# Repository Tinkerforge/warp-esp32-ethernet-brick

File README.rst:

WARP ESP32 Ethernet Brick
=========================

This repository contains the firmware source code and the hardware design
files. The documentation generator configs can be found at
https://github.com/Tinkerforge/generators

.. BEGIN WARP REPOSITORIES (managed block, generated from esp32-firmware/repo_overview.rst - do not edit by hand, run update_repo_overview.py instead)

WARP Repositories
-----------------

This is an overview of all repositories that make up the WARP Charger and
WARP Energy Manager ecosystem.

Please report **any** issue concerning WARP hard- or software in the
`esp32-firmware`_ repository, no matter which repository it originates from.

Software
~~~~~~~~

- `esp32-firmware`_ - Source code of the ESP32 firmware shared between all WARP Chargers and Energy Managers

Libraries used by the firmware:

- `tfjson`_ - SAX style JSON serializer and deserializer
- `tfnetwork`_ - Modbus TCP server and client implementation
- `tfocpp`_ - OCPP 1.6 implementation
- `tftools`_ - Miscellaneous tools and helpers

Remote access:

- `esp32-remote-access`_ - Source code of the my.warp-charger.com remote access server

Documentation, tools and integrations:

- `warp-charger`_ - Source code of (docs.)warp-charger.com and the printed manual, released firmwares, datasheets and documents, as well as some tools and hardware design files
- `api.warp-charger.com`_ - Serves APIs that are used by WARP Chargers to obtain relevant public information like day ahead prices
- `vislog.warp-charger.com`_ - Visualizes WARP Charger logs and EVSE debug protocols
- `dbus-warp-charger`_ - Integrates WARP Chargers into a Victron Energy Venus OS device (e.g. Cerbo GX)

WARP Charger Hardware
~~~~~~~~~~~~~~~~~~~~~~

WARP4 Charger
"""""""""""""

*Current charger generation.*

- `warp-esp32-ethernet-v2-brick`_ - Hardware design files of the WARP ESP32 Ethernet Brick 2.0
- `warp-esp32-ethernet-v2-co-bricklet`_ - Firmware source code of the WARP ESP32 Ethernet 2.0 Co Bricklet (co-processor)
- `evse-v4-bricklet`_ - Hardware design files of the EVSE 4.0 Bricklet (firmware shared with the EVSE 2.0 Bricklet)
- `nfc-bricklet`_ - Firmware source code and hardware design files of the NFC Bricklet

WARP3 Charger
"""""""""""""

- `warp-esp32-ethernet-brick`_ - Hardware design files of the WARP ESP32 Ethernet Brick
- `evse-v3-bricklet`_ - Hardware design files of the EVSE 3.0 Bricklet (firmware shared with the EVSE 2.0 Bricklet)
- `nfc-bricklet`_ - Firmware source code and hardware design files of the NFC Bricklet

WARP2 Charger
"""""""""""""

- `esp32-ethernet-brick`_ - Hardware design files of the ESP32 Ethernet Brick
- `evse-v2-bricklet`_ - Firmware source code and hardware design files of the EVSE 2.0 Bricklet
- `nfc-bricklet`_ - Firmware source code and hardware design files of the NFC Bricklet

WARP1 Charger
"""""""""""""

- `esp32-brick`_ - Hardware design files of the ESP32 Brick
- `evse-bricklet`_ - Firmware source code and hardware design files of the EVSE Bricklet
- `rs485-bricklet`_ - Firmware source code and hardware design files of the RS485 Bricklet

WARP Energy Manager Hardware
~~~~~~~~~~~~~~~~~~~~~~~~~~~~~~

WARP Energy Manager 2.0
"""""""""""""""""""""""

*Current energy manager generation.*

- `esp32-ethernet-brick`_ - Hardware design files of the ESP32 Ethernet Brick
- `warp-energy-manager-v2-bricklet`_ - Firmware source code and hardware design files of the WARP Energy Manager 2.0 Bricklet
- `warp-front-panel-bricklet`_ - Firmware source code and hardware design files of the WARP Front Panel Bricklet

WARP Energy Manager 1.0
"""""""""""""""""""""""

- `esp32-ethernet-brick`_ - Hardware design files of the ESP32 Ethernet Brick
- `warp-energy-manager-bricklet`_ - Firmware source code and hardware design files of the WARP Energy Manager Bricklet

Forked/patched projects
~~~~~~~~~~~~~~~~~~~~~~~~~

- `arduino-esp32`_
- `esp32-arduino-libs`_
- `WireGuard-ESP32-Arduino`_

.. Link targets: One definition per repository, keep in sync with the lists above.

.. _esp32-firmware: https://github.com/Tinkerforge/esp32-firmware
.. _tfjson: https://github.com/Tinkerforge/tfjson
.. _tfnetwork: https://github.com/Tinkerforge/tfnetwork
.. _tfocpp: https://github.com/Tinkerforge/tfocpp
.. _tftools: https://github.com/Tinkerforge/tftools
.. _esp32-remote-access: https://github.com/Tinkerforge/esp32-remote-access
.. _warp-charger: https://github.com/Tinkerforge/warp-charger
.. _api.warp-charger.com: https://github.com/Tinkerforge/api.warp-charger.com
.. _vislog.warp-charger.com: https://github.com/Tinkerforge/vislog.warp-charger.com
.. _dbus-warp-charger: https://github.com/Tinkerforge/dbus-warp-charger
.. _warp-esp32-ethernet-v2-brick: https://github.com/Tinkerforge/warp-esp32-ethernet-v2-brick
.. _warp-esp32-ethernet-v2-co-bricklet: https://github.com/Tinkerforge/warp-esp32-ethernet-v2-co-bricklet
.. _evse-v4-bricklet: https://github.com/Tinkerforge/evse-v4-bricklet
.. _nfc-bricklet: https://github.com/Tinkerforge/nfc-bricklet
.. _warp-esp32-ethernet-brick: https://github.com/Tinkerforge/warp-esp32-ethernet-brick
.. _evse-v3-bricklet: https://github.com/Tinkerforge/evse-v3-bricklet
.. _esp32-ethernet-brick: https://github.com/Tinkerforge/esp32-ethernet-brick
.. _evse-v2-bricklet: https://github.com/Tinkerforge/evse-v2-bricklet
.. _esp32-brick: https://github.com/Tinkerforge/esp32-brick
.. _evse-bricklet: https://github.com/Tinkerforge/evse-bricklet
.. _rs485-bricklet: https://github.com/Tinkerforge/rs485-bricklet
.. _warp-energy-manager-v2-bricklet: https://github.com/Tinkerforge/warp-energy-manager-v2-bricklet
.. _warp-front-panel-bricklet: https://github.com/Tinkerforge/warp-front-panel-bricklet
.. _warp-energy-manager-bricklet: https://github.com/Tinkerforge/warp-energy-manager-bricklet
.. _arduino-esp32: https://github.com/Tinkerforge/arduino-esp32
.. _esp32-arduino-libs: https://github.com/Tinkerforge/esp32-arduino-libs
.. _WireGuard-ESP32-Arduino: https://github.com/Tinkerforge/WireGuard-ESP32-Arduino

.. END WARP REPOSITORIES

Repository Content
------------------

hardware/:
 * Contains KiCad project files and additionally schematics as PDF

datasheets/:
 * Contains datasheets for sensors and complex ICs that are used

Hardware
--------

The hardware is designed with the open source EDA Suite KiCad
(http://www.kicad.org). Before you are able to open the files,
you have to install the Tinkerforge kicad-libraries
(https://github.com/Tinkerforge/kicad-libraries). You can either clone
them directly in hardware/ or clone them in a separate folder and
symlink them into hardware/
(ln -s kicad_path/kicad-libraries project_path/hardware). After that you
can open the .pro file in hardware/ with KiCad and from there view and
modify the schematics and the PCB layout.

Software
--------

The software for all Bricks based on the ESP32 can be found at:
https://github.com/Tinkerforge/esp32-firmware/tree/master/software

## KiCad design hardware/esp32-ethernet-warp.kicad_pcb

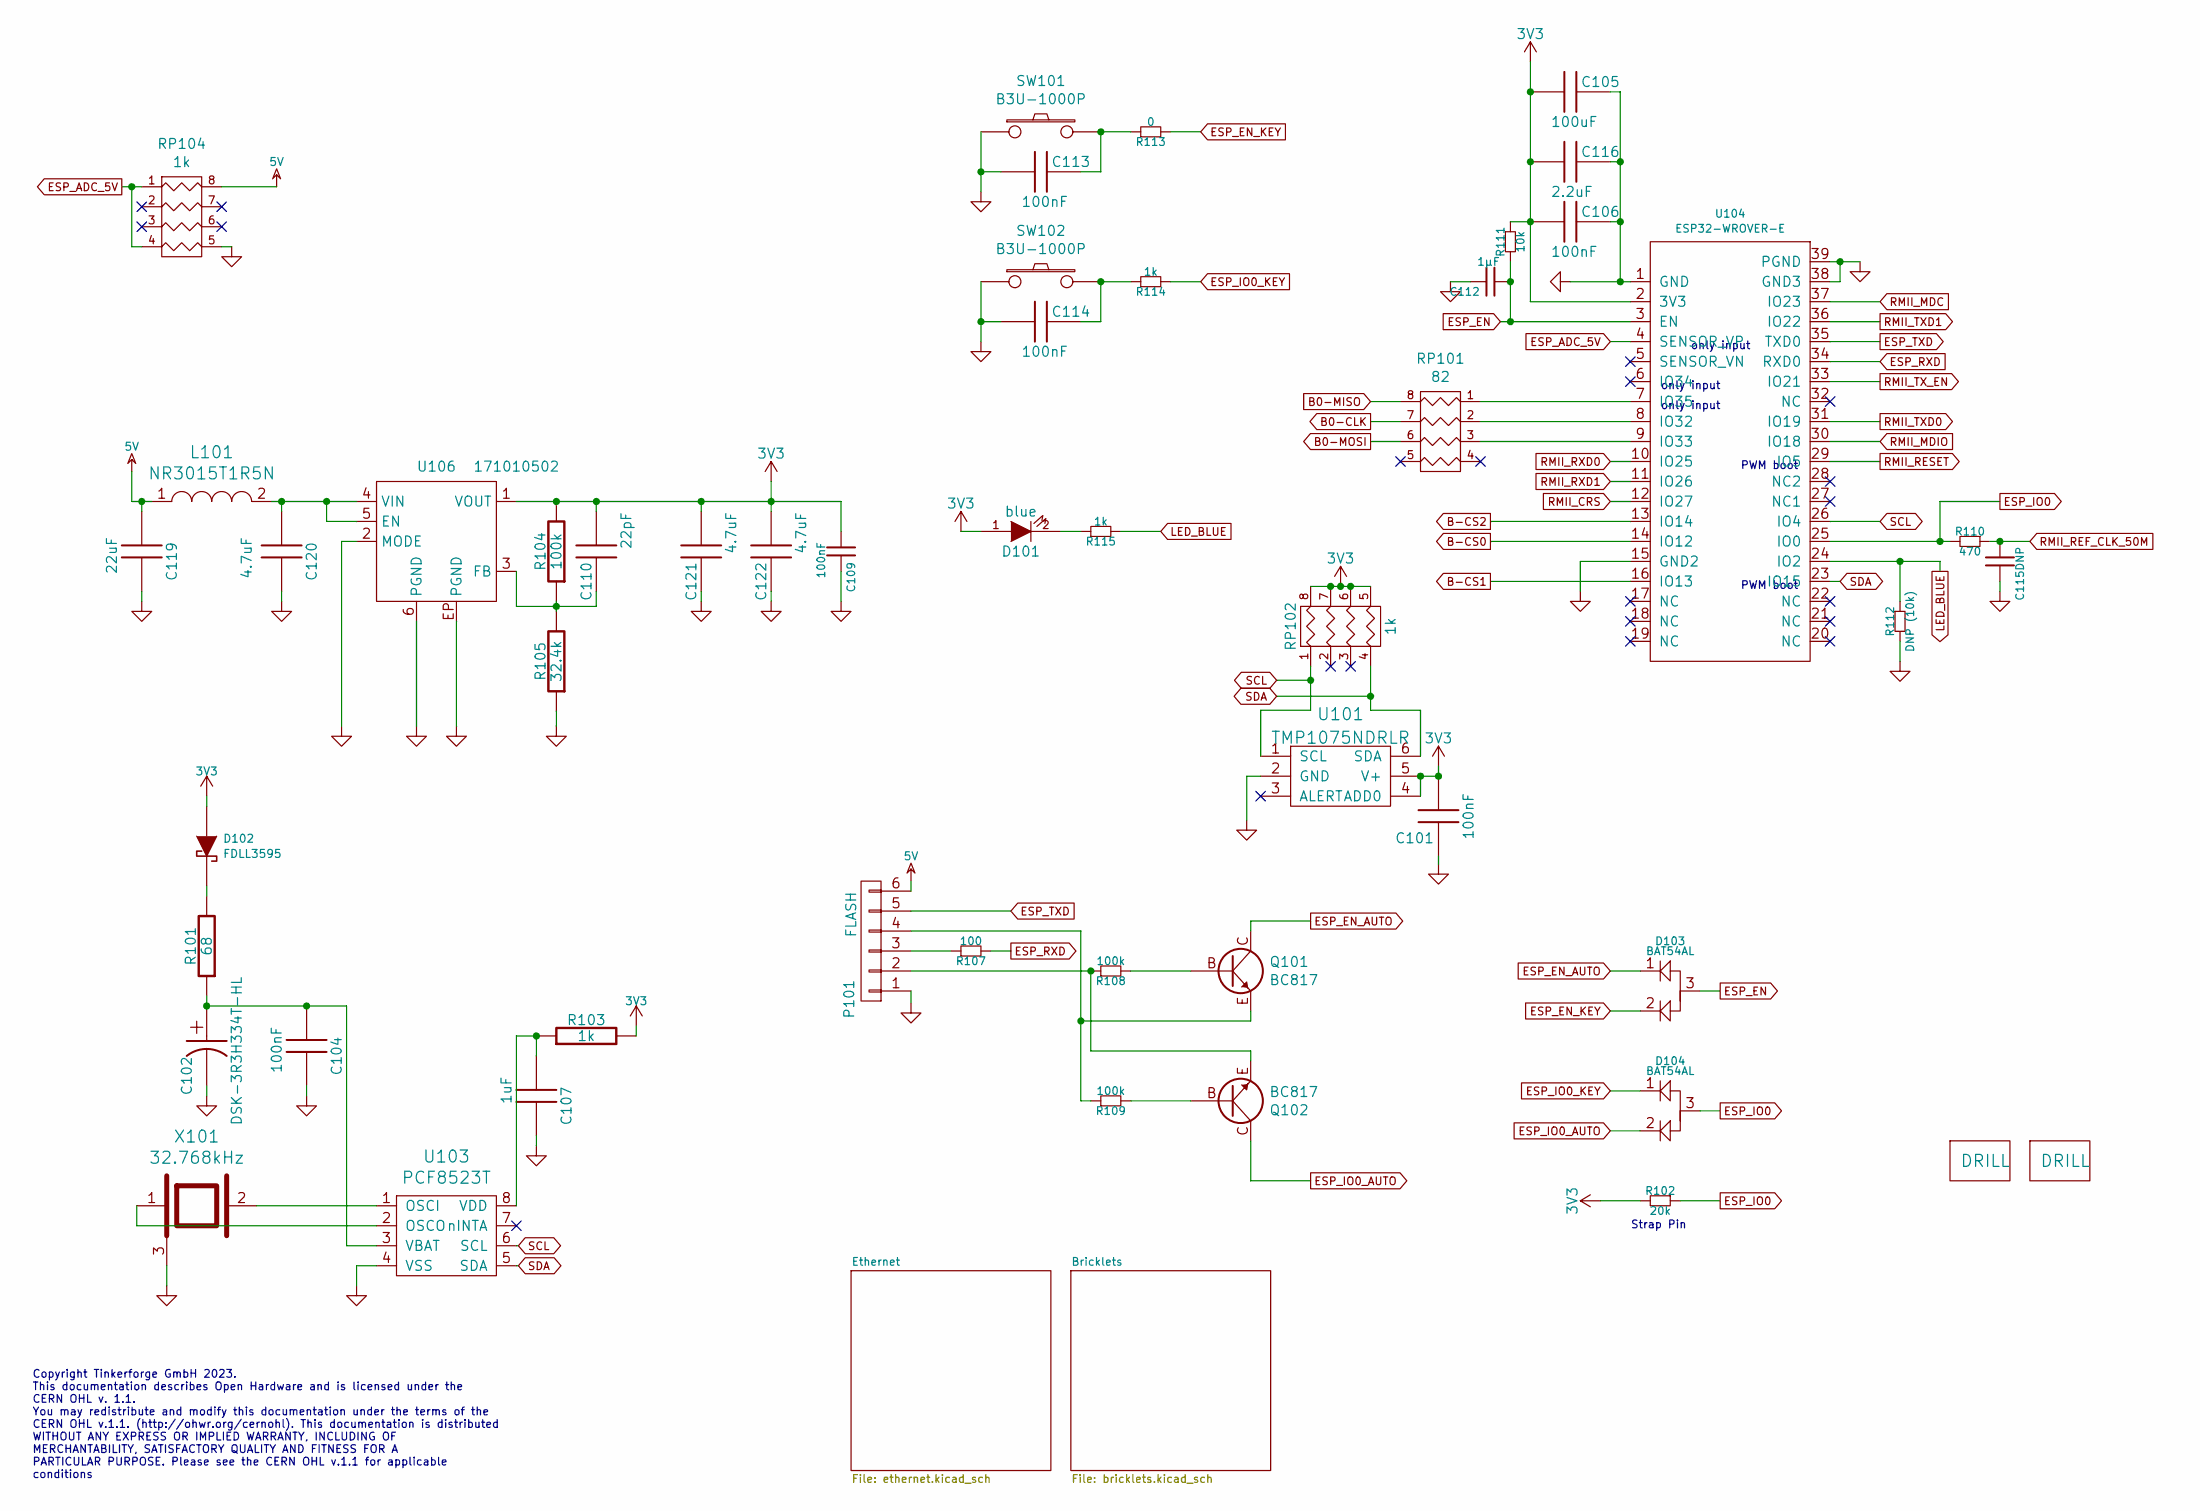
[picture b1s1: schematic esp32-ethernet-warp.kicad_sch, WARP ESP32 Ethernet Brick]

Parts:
C101, C104, C106, C109, C113, C114: 100nF; C0402F
C102: DSK-3R3H334T-HL; DSK
C105: 100uF; C1210
C107: 1uF; C0603F
C110: 22pF; C0402F
C112: 1µF; C0603F
C115: DNP; C0402F
C116: 2.2uF; C0603F
C119: 22uF; C1206
C120, C121, C122: 4.7uF; C0805E
D101: blue; D0603F
D102: FDLL3595; MiniMelf
D103, D104: BAT54AL; SOT23-3
F102, F103: DRILL; LSMTSO-M3
L101: NR3015T1R5N; NR3030
P101: FLASH; pin_array_1x6-P2mm_D1mm
Q101, Q102: BC817; SOT23EBC
R101: 68; R0402F
R102: 20k; R0402F
R103, R114, R115: 1k; R0402F
R104, R108, R109: 100k; R0402F
R105: 32.4k; R0402F
R107: 100; R0402F
R110: 470; R0402F
R111: 10k; R0402F
R112: DNP (10k); R0402F
R113: 0; R0402F
RP101: 82; 4X0402
RP102, RP104: 1k; 4X0402
SW101, SW102: B3U-1000P
U101: TMP1075NDRLR; SOT563
U103: PCF8523T; SO-8
U104: ESP32-WROVER-E
U106: 171010502
X101: 32.768kHz; AB26TRQ

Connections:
3V3: C101.1, C105.2, C106.2, C109.2, C110.2, C116.2, C121.2, C122.2, D101.1 (A), D102.1 (A), R102.2, R103.2, R104.2, R111.1, RP102.5 (R4), RP102.6 (R3), RP102.7 (R2), RP102.8 (R1), U101.4 (ADD0), U101.5 (V+), U104.2 (3V3), U106.1 (VOUT); also elsewhere on the board
5V: C119.2, L101.1, P101.6, RP104.8 (R1); also elsewhere on the board
B0-CLK: RP101.7 (R2); also elsewhere on the board
B0-MISO: RP101.8 (R1); also elsewhere on the board
B0-MOSI: RP101.6 (R3); also elsewhere on the board
B-CS0: U104.14 (IO12); also elsewhere on the board
B-CS1: U104.16 (IO13); also elsewhere on the board
B-CS2: U104.13 (IO14); also elsewhere on the board
ESP_ADC_5V: RP104.1, RP104.4, U104.4 (SENSOR_VP)
ESP_EN: C112.2, D103.3, R111.2, U104.3 (EN)
ESP_EN_AUTO: D103.1, Q101.C
ESP_EN_KEY: D103.2, R113.2
ESP_IO0: D104.3, R102.1, R110.2, U104.25 (IO0)
ESP_IO0_AUTO: D104.2, Q102.C
ESP_IO0_KEY: D104.1, R114.2
ESP_RXD: R107.2, U104.34 (RXD0)
ESP_TXD: P101.5, U104.35 (TXD0)
GND: C101.2, C102.2, C104.1, C105.1, C106.1, C107.1, C109.1, C112.1, C113.2, C114.2, C115.2, C116.1, C119.1, C120.1, C121.1, C122.1, P101.1, R105.1, R112.2, RP104.5 (R4), SW101.1, SW102.1, U101.2 (GND), U103.4 (VSS), U104.1 (GND), U104.15 (GND2), U104.38 (GND3), U104.39 (PGND), U106.2 (MODE), U106.6 (PGND), U106.EP (PGND), X101.3; also elsewhere on the board
LED_BLUE: R112.1, R115.2, U104.24 (IO2)
unnamed: C113.1, R113.1, SW101.2
unnamed: C114.1, R114.1, SW102.2
unnamed: D101.2 (K), R115.1
unnamed: D102.2 (K), R101.2
unnamed: P101.2, Q102.E, R108.1
unnamed: P101.3, R107.1
unnamed: P101.4, Q101.E, R109.1
unnamed: Q101.B, R108.2
unnamed: Q102.B, R109.2
unnamed: RP101.1, U104.7 (IO35)
unnamed: RP101.2, U104.8 (IO32)
unnamed: RP101.3, U104.9 (IO33)
unnamed: U103.1 (OSCI), X101.2
unnamed: U103.2 (OSCO), X101.1
unnamed: C102.1, C104.2, R101.1, U103.3 (VBAT)
unnamed: C107.2, R103.1, U103.8 (VDD)
unnamed: C120.2, L101.2, U106.4 (VIN), U106.5 (EN)
unnamed: C110.1, R104.1, R105.2, U106.3 (FB)
RMII_CRS: U104.12 (IO27); also elsewhere on the board
RMII_MDC: U104.37 (IO23); also elsewhere on the board
RMII_MDIO: U104.30 (IO18); also elsewhere on the board
RMII_REF_CLK_50M: C115.1, R110.1; also elsewhere on the board
RMII_RESET: U104.29 (IO5); also elsewhere on the board
RMII_RXD0: U104.10 (IO25); also elsewhere on the board
RMII_RXD1: U104.11 (IO26); also elsewhere on the board
RMII_TXD0: U104.31 (IO19); also elsewhere on the board
RMII_TXD1: U104.36 (IO22); also elsewhere on the board
RMII_TX_EN: U104.33 (IO21); also elsewhere on the board
SCL: RP102.1, U101.1 (SCL), U103.6 (SCL), U104.26 (IO4)
SDA: RP102.4, U101.6 (SDA), U103.5 (SDA), U104.23 (IO15)

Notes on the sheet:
Strap Pin
only input
Copyright Tinkerforge GmbH 2023. This documentation describes Open Hardware and is licensed under the CERN OHL v. 1.1. You may redistribute and modify this documentation under the terms of the CERN OHL v.1.1. (http://ohwr.org/cernohl). This documentation is distributed WITHOUT ANY EXPRESS OR IMPLIE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
PWM boot

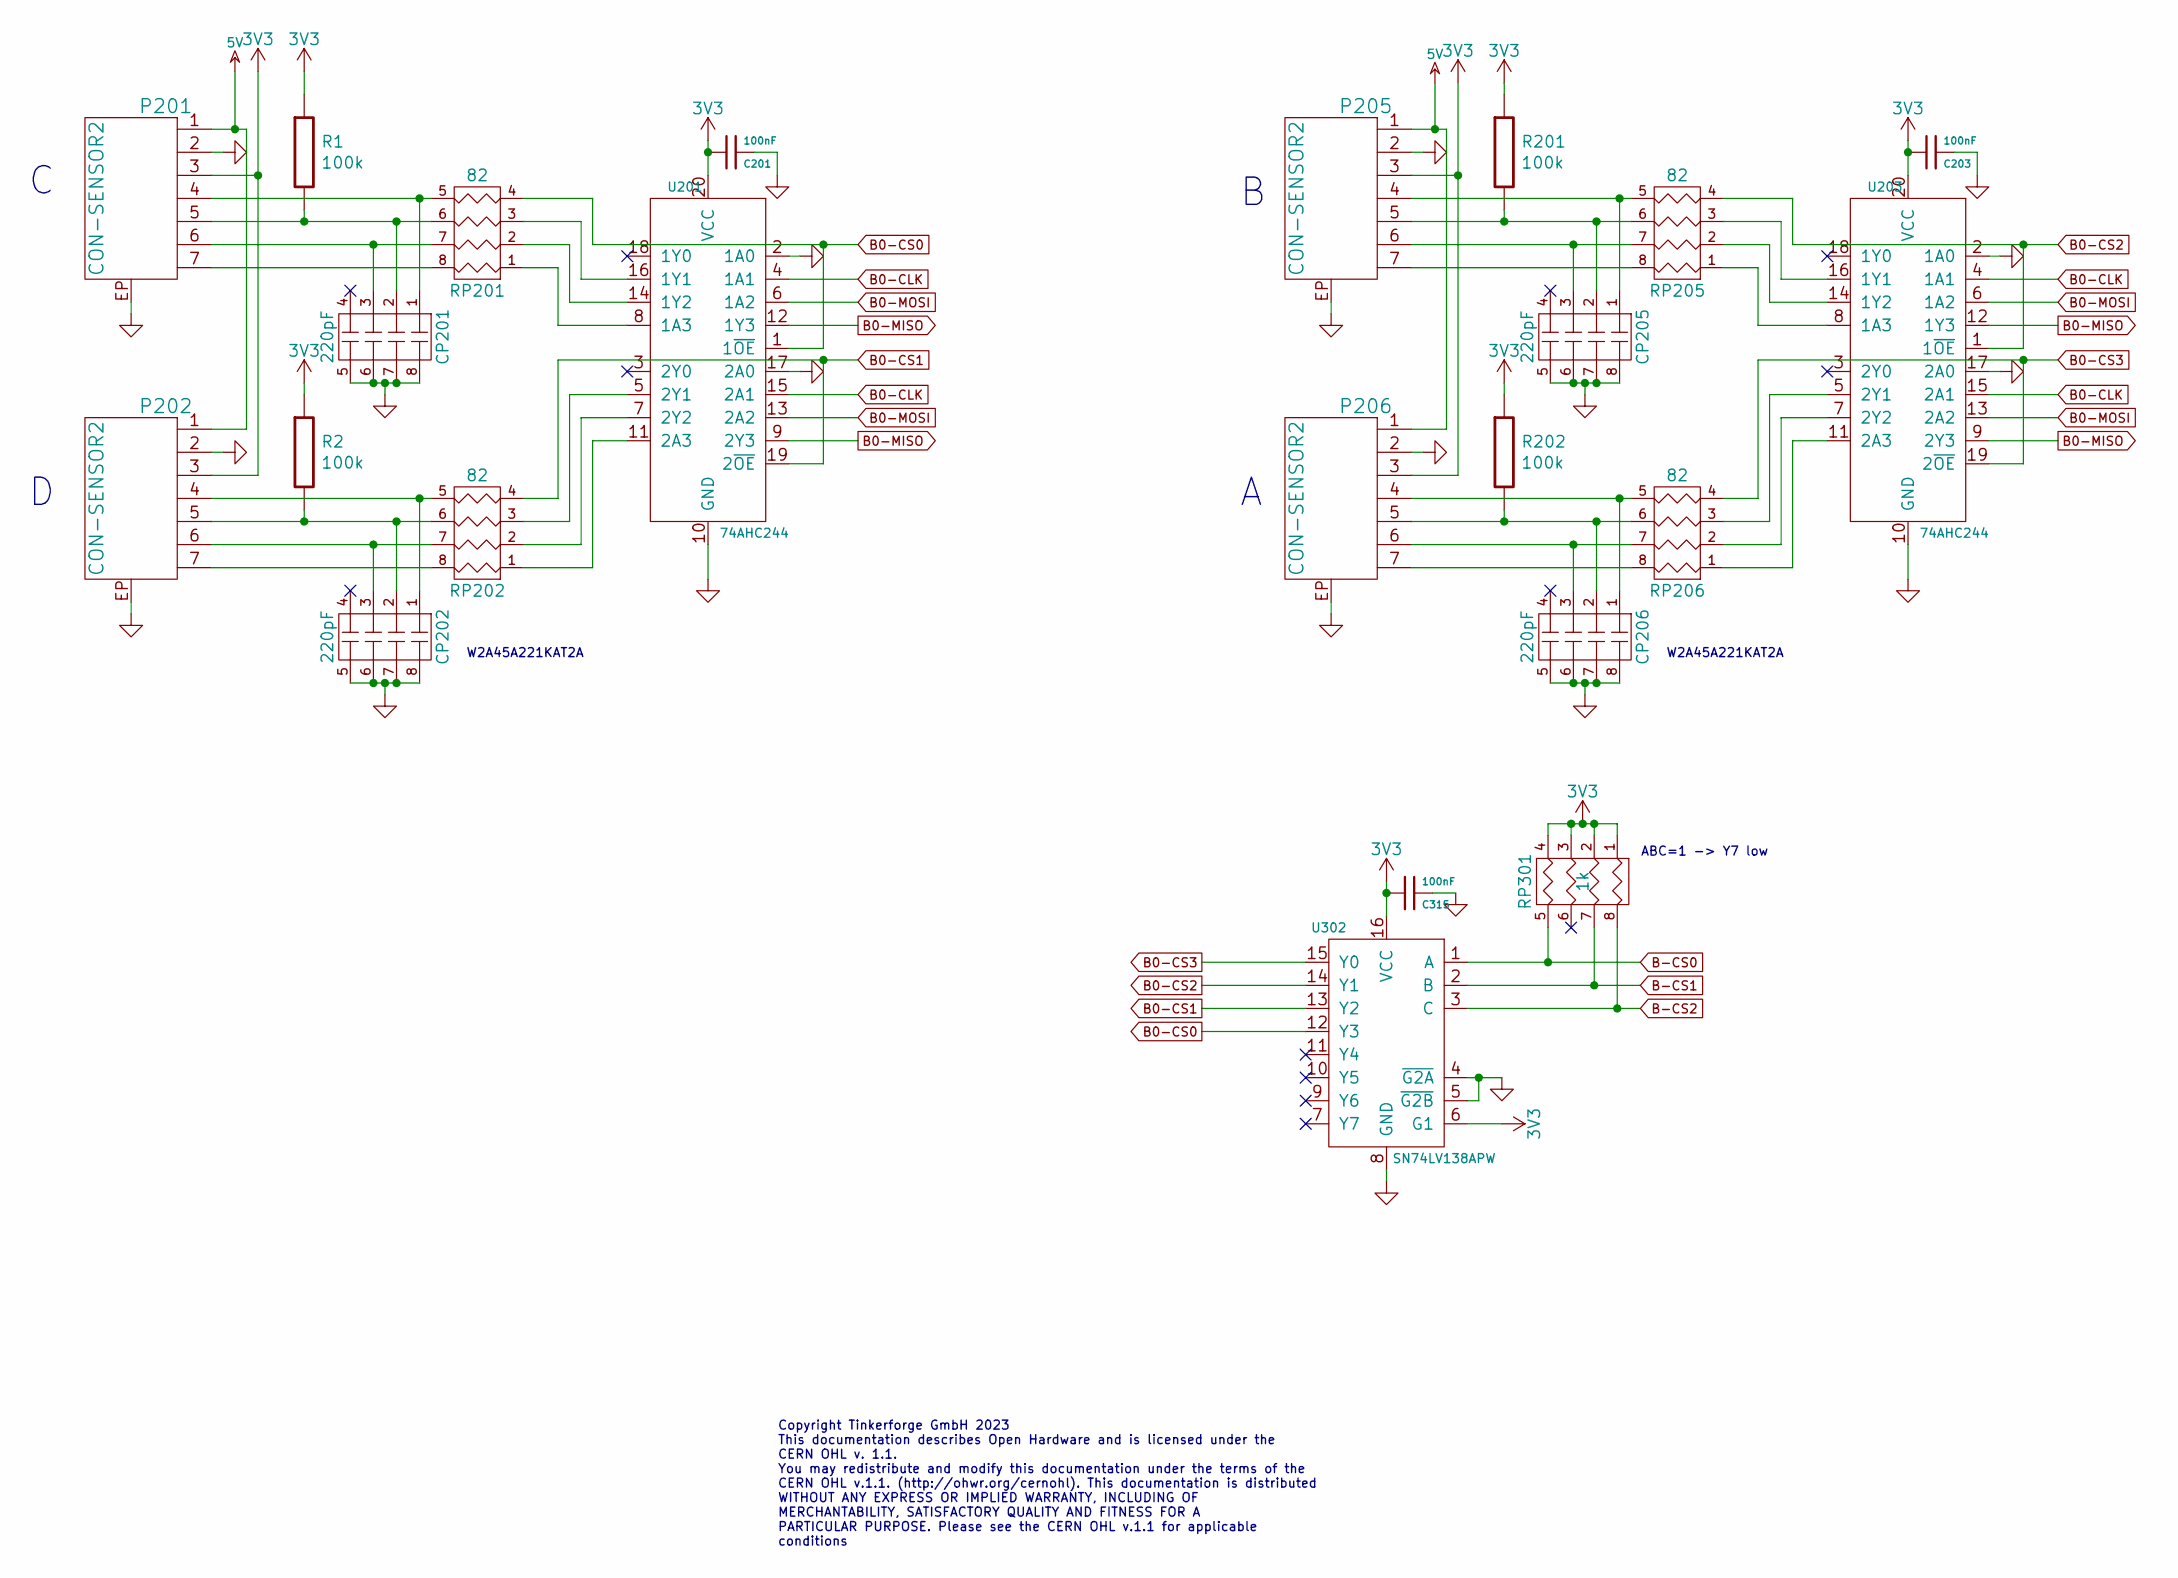
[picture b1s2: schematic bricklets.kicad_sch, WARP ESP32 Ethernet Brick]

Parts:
C201, C203, C315: 100nF; C0402F
CP201, CP202, CP205, CP206: 220pF; 4X0402
P201, P202, P205, P206: CON-SENSOR2
R1, R2, R201, R202: 100k; R0402F
RP201, RP202, RP205, RP206: 82; 4X0402
RP301: 1k; 4X0402
U201, U203: 74AHC244; TSSOP20
U302: SN74LV138APW; TSSOP16

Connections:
3V3: C201.2, C203.2, C315.2, P201.3, P202.3, P205.3, P206.3, R1.1, R2.1, R201.1, R202.1, RP301.1, RP301.2, RP301.3, RP301.4, U201.20 (VCC), U203.20 (VCC), U302.6 (G1), U302.16 (VCC); also elsewhere on the board
5V: P201.1, P202.1, P205.1, P206.1; also elsewhere on the board
B0-CLK: U201.4 (1A1), U201.15 (2A1), U203.4 (1A1), U203.15 (2A1); also elsewhere on the board
B0-CS0: RP201.4, U201.1 (1~OE), U302.12 (Y3)
B0-CS1: RP202.4, U201.19 (2~OE), U302.13 (Y2)
B0-CS2: RP205.4, U203.1 (1~OE), U302.14 (Y1)
B0-CS3: RP206.4, U203.19 (2~OE), U302.15 (Y0)
B0-MISO: U201.9 (2Y3), U201.12 (1Y3), U203.9 (2Y3), U203.12 (1Y3); also elsewhere on the board
B0-MOSI: U201.6 (1A2), U201.13 (2A2), U203.6 (1A2), U203.13 (2A2); also elsewhere on the board
B-CS0: RP301.5 (R4), U302.1 (A); also elsewhere on the board
B-CS1: RP301.7 (R2), U302.2 (B); also elsewhere on the board
B-CS2: RP301.8 (R1), U302.3 (C); also elsewhere on the board
GND: C201.1, C203.1, C315.1, CP201.5 (R4), CP201.6 (R3), CP201.7 (R2), CP201.8 (R1), CP202.5 (R4), CP202.6 (R3), CP202.7 (R2), CP202.8 (R1), CP205.5 (R4), CP205.6 (R3), CP205.7 (R2), CP205.8 (R1), CP206.5 (R4), CP206.6 (R3), CP206.7 (R2), CP206.8 (R1), P201.2, P201.EP, P202.2, P202.EP, P205.2, P205.EP, P206.2, P206.EP, U201.2 (1A0), U201.10 (GND), U201.17 (2A0), U203.2 (1A0), U203.10 (GND), U203.17 (2A0), U302.4 (~G2A), U302.5 (~G2B), U302.8 (GND); also elsewhere on the board
unnamed: CP201.1, P201.4, RP201.5 (R4)
unnamed: CP201.2, P201.5, R1.2, RP201.6 (R3)
unnamed: CP201.3, P201.6, RP201.7 (R2)
unnamed: CP202.1, P202.4, RP202.5 (R4)
unnamed: CP202.2, P202.5, R2.2, RP202.6 (R3)
unnamed: CP202.3, P202.6, RP202.7 (R2)
unnamed: CP205.1, P205.4, RP205.5 (R4)
unnamed: CP205.2, P205.5, R201.2, RP205.6 (R3)
unnamed: CP205.3, P205.6, RP205.7 (R2)
unnamed: CP206.1, P206.4, RP206.5 (R4)
unnamed: CP206.2, P206.5, R202.2, RP206.6 (R3)
unnamed: CP206.3, P206.6, RP206.7 (R2)
unnamed: RP201.1, U201.8 (1A3)
unnamed: RP201.2, U201.14 (1Y2)
unnamed: RP201.3, U201.16 (1Y1)
unnamed: P201.7, RP201.8 (R1)
unnamed: RP202.1, U201.11 (2A3)
unnamed: RP202.2, U201.7 (2Y2)
unnamed: RP202.3, U201.5 (2Y1)
unnamed: P202.7, RP202.8 (R1)
unnamed: RP205.1, U203.8 (1A3)
unnamed: RP205.2, U203.14 (1Y2)
unnamed: RP205.3, U203.16 (1Y1)
unnamed: P205.7, RP205.8 (R1)
unnamed: RP206.1, U203.11 (2A3)
unnamed: RP206.2, U203.7 (2Y2)
unnamed: RP206.3, U203.5 (2Y1)
unnamed: P206.7, RP206.8 (R1)

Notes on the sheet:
Copyright Tinkerforge GmbH 2023 This documentation describes Open Hardware and is licensed under the CERN OHL v. 1.1. You may redistribute and modify this documentation under the terms of the CERN OHL v.1.1. (http://ohwr.org/cernohl). This documentation is distributed WITHOUT ANY EXPRESS OR IMPLIED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
W2A45A221KAT2A
ABC=1 -> Y7 low

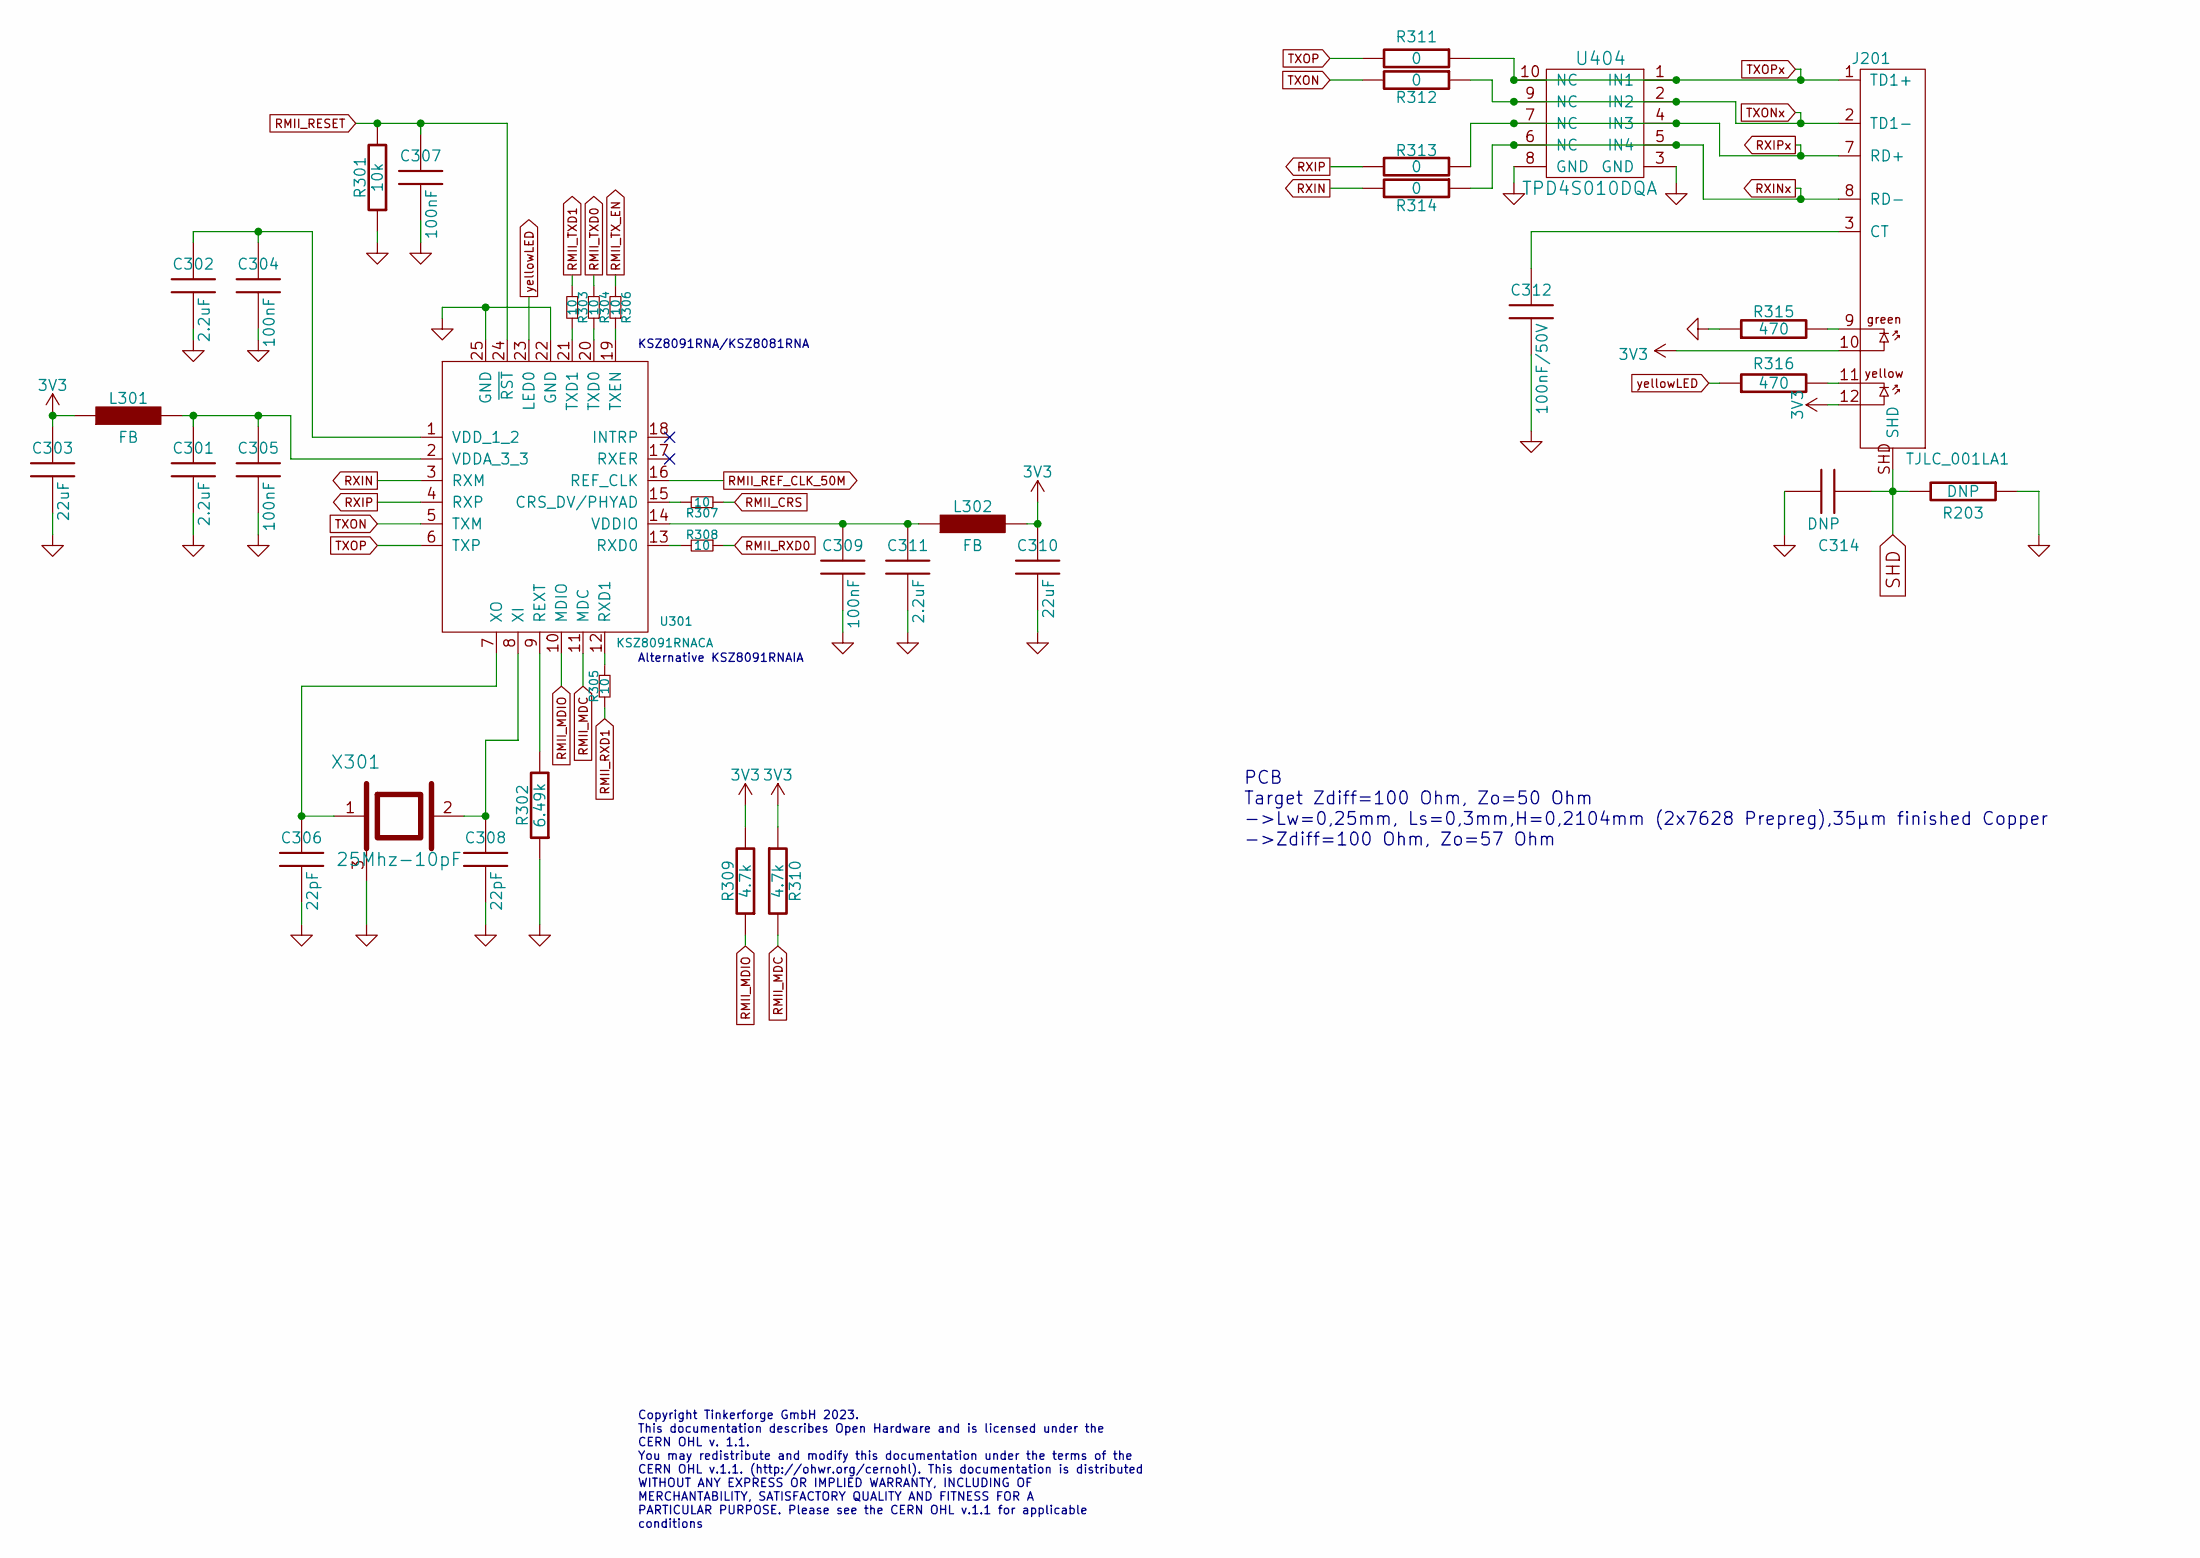
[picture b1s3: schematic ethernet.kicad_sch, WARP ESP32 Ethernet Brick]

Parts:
C301, C302, C311: 2.2uF; C0603F
C303, C310: 22uF; C1206
C304, C305, C307, C309: 100nF; C0402F
C306, C308: 22pF; C0402F
C312: 100nF/50V; C0402F
C314: DNP; C1206
J201: TJLC_001LA1; TJLC-001LA1
L301, L302: FB; R0603F
R203: DNP; 1812
R301: 10k; R0402F
R302: 6.49k; R0402F
R303, R304, R305, R306, R307, R308: 10; R0402F
R309, R310: 4.7k; R0402F
R311, R312, R313, R314: 0; R0402F
R315, R316: 470; R0402F
U301: KSZ8091RNACA; QFN-24-4x4-EP
U404: TPD4S010DQA
X301: 25Mhz-10pF; CRYSTAL_3225

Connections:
3V3: C303.2, C310.2, J201.10, J201.12, L301.1, L302.2, R309.2, R310.1; also elsewhere on the board
GND: C301.1, C302.1, C303.1, C304.1, C305.1, C306.1, C307.1, C308.1, C309.1, C310.1, C311.1, C312.1, C314.2, R203.1, R301.1, R302.1, R315.1, U301.22 (GND), U301.25 (GND), X301.3; also elsewhere on the board
unnamed: C312.2, J201.3 (CT)
unnamed: J201.9, R315.2
unnamed: J201.11, R316.2
unnamed: R307.1, U301.15 (CRS_DV/PHYAD)
unnamed: R302.2, U301.9 (REXT)
unnamed: R308.2, U301.13 (RXD0)
unnamed: R305.1, U301.12 (RXD1)
unnamed: R304.1, U301.20 (TXD0)
unnamed: R303.1, U301.21 (TXD1)
unnamed: R306.1, U301.19 (TXEN)
unnamed: C301.2, C305.2, L301.2, U301.2 (VDDA_3_3)
unnamed: C309.2, C311.2, L302.1, U301.14 (VDDIO)
unnamed: C302.2, C304.2, U301.1 (VDD_1_2)
unnamed: C308.2, U301.8 (XI), X301.2
unnamed: C306.2, U301.7 (XO), X301.1
RMII_CRS: R307.2; also elsewhere on the board
RMII_MDC: R310.2, U301.11 (MDC); also elsewhere on the board
RMII_MDIO: R309.1, U301.10 (MDIO); also elsewhere on the board
RMII_REF_CLK_50M: U301.16 (REF_CLK); also elsewhere on the board
RMII_RESET: C307.2, R301.2, U301.24 (~RST); also elsewhere on the board
RMII_RXD0: R308.1; also elsewhere on the board
RMII_RXD1: R305.2; also elsewhere on the board
RMII_TXD0: R304.2; also elsewhere on the board
RMII_TXD1: R303.2; also elsewhere on the board
RMII_TX_EN: R306.2; also elsewhere on the board
RXIN: R314.2, U301.3 (RXM)
RXINx: J201.8 (RD-), R314.1; also elsewhere on the board
RXIP: R313.2, U301.4 (RXP)
RXIPx: J201.7 (RD+), R313.1; also elsewhere on the board
SHD: C314.1, J201.SHD, R203.2
TXON: R312.2, U301.5 (TXM)
TXONx: J201.2 (TD1-), R312.1; also elsewhere on the board
TXOP: R311.2, U301.6 (TXP)
TXOPx: J201.1 (TD1+), R311.1; also elsewhere on the board
yellowLED: R316.1, U301.23 (LED0)

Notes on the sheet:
KSZ8091RNA/KSZ8081RNA
PCB Target Zdiff=100 Ohm, Zo=50 Ohm ->Lw=0,25mm, Ls=0,3mm,H=0,2104mm (2x7628 Prepreg),35µm finished Copper ->Zdiff=100 Ohm, Zo=57 Ohm
Alternative KSZ8091RNAIA
Copyright Tinkerforge GmbH 2023. This documentation describes Open Hardware and is licensed under the CERN OHL v. 1.1. You may redistribute and modify this documentation under the terms of the CERN OHL v.1.1. (http://ohwr.org/cernohl). This documentation is distributed WITHOUT ANY EXPRESS OR IMPLIE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

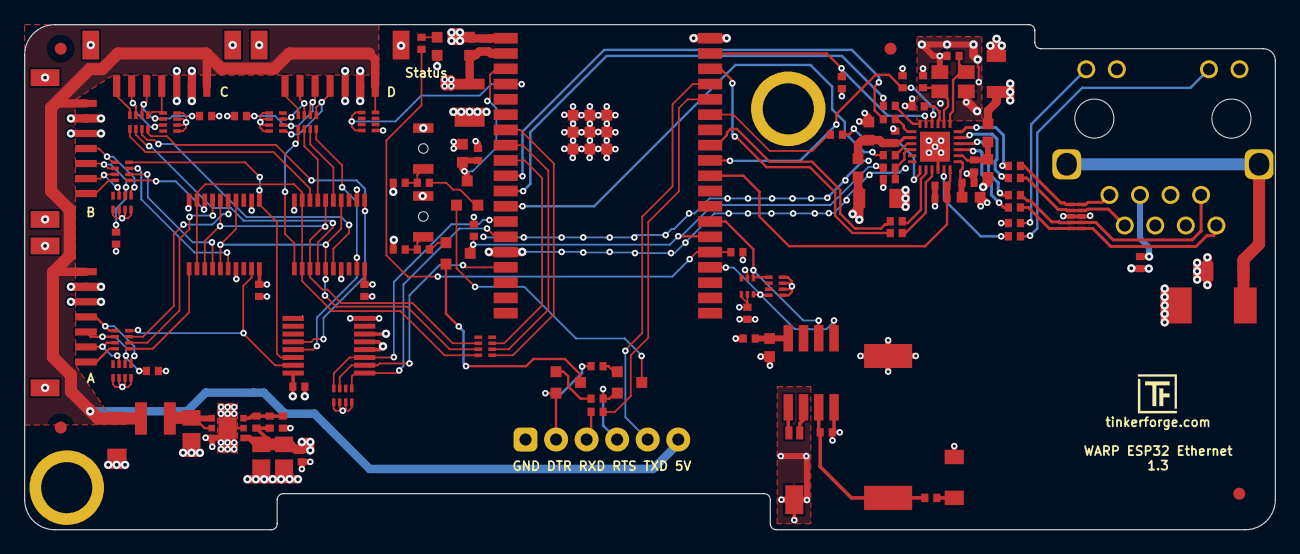
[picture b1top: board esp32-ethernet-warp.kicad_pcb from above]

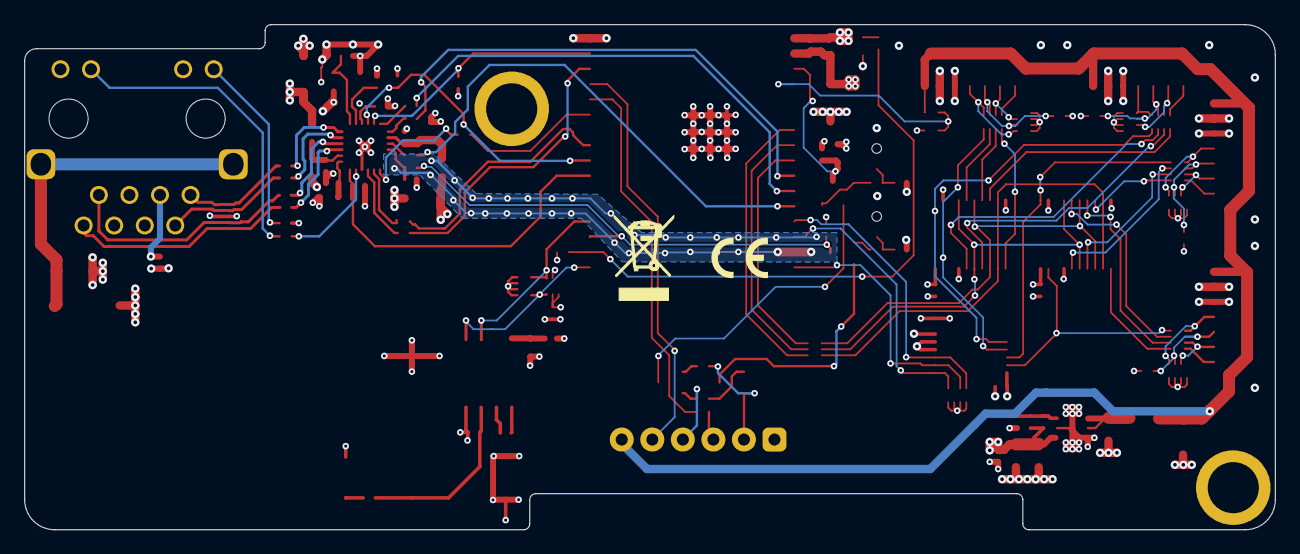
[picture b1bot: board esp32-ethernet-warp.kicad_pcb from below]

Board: 4 copper layers, 104.0 x 42.0 mm, 116 parts (3 on the bottom side), 106 nets.

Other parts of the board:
Fiducial_Mark: VAL**; Fiducial_Mark
Fiducial_Mark#2, Fiducial_Mark#3, Fiducial_Mark#4: VAL**; Fiducial_Mark
U202: TPD4S010DQA
VAL: WEEE_7mm
VAL#2: CE_5mm

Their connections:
GND: U202.3 (GND), U202.8 (GND); also elsewhere on the board
RXINx: U202.5 (IN4), U202.6 (NC); also elsewhere on the board
RXIPx: U202.4 (IN3), U202.7 (NC); also elsewhere on the board
TXONx: U202.2 (IN2), U202.9 (NC); also elsewhere on the board
TXOPx: U202.1 (IN1), U202.10 (NC); also elsewhere on the board

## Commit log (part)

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2024-01-12 move hardware files to correct git repo
2024-01-12 Fix name
2024-01-12 Add hint that software can be found in esp32-firmware git
2024-02-01 mark C314 as DNP
2025-07-16 README: Add repo overview.

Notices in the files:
hardware/bricklets.kicad_sch:
Licensed under CERN OHL v.1.1
Copyright (©) 2023, B.Nordmeyer
